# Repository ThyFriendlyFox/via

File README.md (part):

# Via

[Website](https://via.computer) · [Contract](WORKCENTER.md) · [Status](ee-agent-kit/STATUS.md) · [Roadmap](ee-agent-kit/ROADMAP.md)

Via is a workcenter: a set of tools, skills and gates
that an agent steps into to do one kind of work well. Via does
electronics: it turns a KiCad 10 project into fabrication outputs that
passed every gate.

A new board starts with 2 commands. `workcenter new <dir>` writes the
project: a design file to edit, from the template. `workcenter next <dir>`
then names each step, 1 at a time, until the board is GREEN.

<a href="https://via.computer">
  <picture>
    <source media="(prefers-color-scheme: dark)" srcset="site/media/hero-dark.png">
    
  </picture>
</a>

The fixture board `tests/boards/pass-first-design`: lines of its design
file, then the schematic and the routed board that `workcenter design`
writes from the file. The middle card shows the circuit's part of the
sheet.

2 runs of the gates, as the terminal printed them: that board, and a
fixture board with a clearance error on purpose.

```text
$ workcenter gates tests/boards/pass-first-design
PASS   erc        0 errors, 0 warnings  [0.25s]
PASS   drc        0 errors, 0 warnings (0 unconnected, 0 parity), legend (no fab named: held to the least of the 4 fabs Via knows (height pcbway-standard, stroke oshpark-2layer)): 0 fail, 0 not judged  [0.76s]
PASS   sim        1 decks, 46 corner runs, 0 failures  [0.16s]
PASS   export     7/7 outputs, 22 gerber files, 3 files read back  [2.09s]
thermal: no part's junction is judged: sim/thermal.json is not there (the simulate skill, A part's temperature, step 3)
thermal: no part of the board carries a thermal figure in its facts, so no junction is asked for (4 parts; 3 with no facts entry, which `workcenter ratings` names)
RATINGS not asked for: no ratings.json beside the schematic
GREEN: divider  report /home/user/via/tests/boards/pass-first-design/build/gates.json

$ workcenter gates tests/boards/fail-drc-clearance
PASS   erc        0 errors, 0 warnings  [0.3s]
FAIL   drc        1 errors, 1 warnings (0 unconnected, 0 parity), legend (no fab named: held to the least of the 4 fabs Via knows (height pcbway-standard, stroke oshpark-2layer)): 0 fail, 0 not judged  [0.65s]
       - error: clearance: Clearance violation ( clearance 0.2000 mm; actual 0.0500 mm)
       - warning: track_dangling: Track has unconnected end
RATINGS not asked for: no ratings.json beside the schematic
RED: rc_divider  report /home/user/via/tests/boards/fail-drc-clearance/build/gates.json
```

<table>
  <tr>
    <td width="50%"></td>
    <td width="50%"></td>
  </tr>
  <tr>
    <td>The same board, turned. <code>workcenter render</code> draws it with <code>--views spin</code>.</td>
    <td>Each layer that holds something. <code>workcenter render</code> draws 1 picture for each and this sheet.</td>
  </tr>
</table>

The 3D views show the part bodies of KiCad's own library. `install.sh`
installs none of them, and without them the same command draws the bare
board. [site/media/README.md](site/media/README.md) has each picture, how
to fetch the 3 bodies, and the whole command that draws it.

## An example: Herald, a fire alarm communicator

[`examples/fire-alarm-communicator/v0.1`](examples/fire-alarm-communicator/v0.1/README.md) sits
beside a fire alarm panel and reports to a monitoring station over LTE-M, with Wi-Fi as the second
path. 84.4 x 64 mm, 4 layers, every part on the front, red with a white legend and black terminals.
It answers the panel's own phone dialer as if it were the line: a current-limited loop feed, dial
tone and the handshake from a PWM pin, and the panel's DTMF digits decoded in firmware with a
Goertzel filter. 3 supervised inputs read a closed contact, a whole loop and a cut wire apart at
every corner, and a fail-safe relay tells the panel when Herald itself fails.

## An example: Rosetta, a universal controller

[`examples/universal-controller/v0.3`](examples/universal-controller/v0.3/README.md) is a wireless game
controller made with Via: a 5-position knob picks a PS4, a PS5, an Xbox, a Switch or
Bluetooth. Its board is laid out like an Xbox 360 controller's, 148 x 82 mm, 6 layers, routed
and GREEN: thumbsticks soldered on (the footprint written from ALPS's drawing), each in a ring of 8
RGB LEDs; Hall-effect triggers on the shoulder horns; an OLED screen under the dip; 2 back buttons
that set any button to rapid, staggered, burst or pulsed turbo; a cell charged at up to 2.5 A from
USB-C, with a fuel gauge, a buck-boost to 3.3 V, and a power path that runs it as a wired controller
when the cell is flat. An RP2040 runs a second USB port in software to relay a console's signature
to a licensed donor, an ESP32's antenna hangs past the dip between the horns, and 6 decks prove the
knob's 5 positions never meet.

## An example: Signet, a mouse worn as a ring

[`examples/ring-mouse`](examples/ring-mouse/README.md) is a mouse you wear on the index finger, made
with Via as a series of prototypes, a version per pass of a loop. Eight 4-layer boards,
12 mm along the finger, sit on the faces of an octagonal prism round it, each soldered to the next by
8 plated edge pads. The ring turns with the hand and the cursor follows its gyroscope; the thumb slides
along a 3-channel strip to scroll and presses the side to click. A Bluetooth LE module, a charger,
a 3.3 V rail and a 20 mAh cell ride on the other tiles, and every tile is GREEN.

## An example: Hush, a speaker that cancels noise

<table>
  <tr>
    <td width="50%"></td>
    <td width="50%"></td>
  </tr>
</table>

[`examples/anc-speaker/v0.1`](examples/anc-speaker/v0.1/README.md) is a ring 62 mm across that
sits on the face of a 40 mm speaker. A microphone on its hub listens 4 mm in front of the cone, and
an analog feedback loop plays the inverse of what it hears: 7 decks hold 3 dB less noise at 50 Hz
and 12 dB from 200 to 300 Hz at every one of 986 corner runs, and take a 150 Hz hum 18.8 dB down
(13.4 dB at the worst corner). Music from a phone plays through the loop as its target. The back
draws the idea: the noise and its inverse, meeting as one line.

## An example: Wyvern, a Snapdragon development board

[`examples/snapdragon-dev-board`](examples/snapdragon-dev-board/README.md) is a development board
with a Snapdragon on it, laid out like a Teensy and kept as version folders. v0.2 is one flat board,
76.2 x 53.34 mm, 6 layers, 2 rows of 30 pins: a Qualcomm QCS6490 on Vantron's VOSM6490 is soldered
straight on by its 662 pads, a land pattern generated from SGET's OSM standard. An RP2350 beside it
drives the pins at 3.3 V, and Linux flashes it over USB. A buck-boost holds the module's 5.0 V from
any USB-C cable, and an HD3SS3220 switches its USB 3 lane to the side the plug is on; the lane and
the converter's 0.25 mm power pads are drawn by hand in the design file.

## An example: Basalt, a microATX Threadripper board

[`examples/threadripper-matx`](examples/threadripper-matx/README.md) is a workstation motherboard
for an AMD Threadripper on sTR5, on a microATX board (244 x 244 mm), which no maker has built. It is
a prototype series built in a loop logged in its [`LOOP.md`](examples/threadripper-matx/LOOP.md),
one version a feature, each GREEN: v0.1 the floor plan, a 4844-land socket and 14 phases with every
supply in a pour; v0.2 the 4 DDR5 channels, 576 traces drawn by rule with 0 DRC errors on the first
run; v0.3 the ports and headers a desktop board carries, routed by the project's own grid router.
10 layers, black and silver.

## A chip: acc8, an 8-bit processor

Via also takes a chip from RTL to a GDSII mask layout: the drawing a
foundry etches from. The project is Verilog, benches, timing constraints
and `chip.json`. 10 gates run in order on open engines and the open
SkyWater 130 nm process, and stop at the first that does not pass.

<table>
  <tr>
    <td width="50%"></td>
    <td width="50%"></td>
  </tr>
  <tr>
    <td>The layout of <code>tests/chips/pass-acc8</code>, every layer: 760 cells on a die of 152.38 um by 152.38 um. <code>workcenter chip render</code> draws it.</td>
    <td>The second metal layer alone. The command draws 1 picture for each routing layer.</td>
  </tr>
</table>

acc8 is an accumulator processor with 16 opcodes and 4 programs in its
ROM. 5 benches make 1098 checks on the RTL, 4 of them again on the
routed netlist. The run, as the terminal printed it:

```text
$ workcenter chip gates tests/chips/pass-acc8 --strict
PASS   lint       4 RTL files, top acc8, 0 failures  [0.19s]
PASS   sim        5 benches, 1098 checks, 18 of 18 changes of the RTL caught, 0 failures  [0.74s]
PASS   synth      760 cells, 132 flops, 8530.7 um2, the mapping removed 24 flops that nothing reads (--json names each), 0 failures  [1.84s]
PASS   layout     8379.29 um2 of cells, utilisation 0.493, 0 failures  [194.64s]
PASS   sta        15 corners, least setup slack 25.1717 ns at max_ss_n40C_1v60, least hold slack 0.2974 ns at min_ff_n40C_1v95, 0 failures  [4.56s]
PASS   glsim      4 benches on the final netlist, 1 on the RTL only, 0 failures  [0.51s]
PASS   drc        2 decks: magic 0, klayout-mr 0, 0 failures  [15.16s]
PASS   antenna    the routed database, 0 failures  [0.31s]
PASS   lvs        the layout against the netlist with its supply pins: 792 devices against 792, 0 failures  [2.82s]
PASS   export     22 files, 20 reports and manifest.json in chip/tapeout, 0 failures  [0.37s]
scope: open engines, sky130A 1.0.470-0-g6d4d117, decks: magic (community), klayout-mr (community), corners: max_ss_n40C_1v60, max_ss_100C_1v60, max_ff_n40C_1v95, max_ff_100C_1v95, max_tt_025C_1v80, min_ss_n40C_1v60, min_ss_100C_1v60, min_ff_n40C_1v95, min_ff_100C_1v95, min_tt_025C_1v80, nom_ss_n40C_1v60, nom_ss_100C_1v60, nom_ff_n40C_1v95, nom_ff_100C_1v95, nom_tt_025C_1v80; no foundry deck ran; no shuttle's limits were checked
GREEN: pass-acc8  report /home/user/via/tests/chips/pass-acc8/build/gates.json
```

| Gate | What it holds |
|---|---|
| LINT, SIM | The RTL reads the same to a simulator and to a synthesizer. Every bench passes, and every listed change of the RTL fails a bench: a bench that passes on a wrong design proves nothing. |
| SYNTH, LAYOUT | The RTL maps onto the library's cells, with a reset on every flop. The cells are placed and routed with no violation. |
| STA, GLSIM | Timing holds at every corner of temperature and supply the project names, with the routed wires. The benches pass again on the routed netlist. |
| DRC, ANTENNA, LVS | The layout breaks no rule of 2 decks, no wire collects too much charge, and the layout is the netlist, device by device. |
| EXPORT | The layout is handed out only when each of the 9 gates passed on the files as they are now. |

The line before the verdict is the scope of the run. GREEN says that the
open engines found no fault in these files. It does not say that a foundry
accepts the layout or that the silicon works: no foundry deck runs here.

The engines install on request: `sudo ./install.sh --chip`.
`workcenter chip init <dir> --top <module>` starts a project, and
`workcenter next <dir>` names each step from there.
[`.claude/skills/chip-design/SKILL.md`](.claude/skills/chip-design/SKILL.md)
has the procedure, and [`tests/chips/README.md`](tests/chips/README.md)
the 9 fixture chips.

## What it does

| Part | In short |
|---|---|
| **Engines** | KiCad 10 (`kicad-cli`), ngspice, FreeRouting. |
| **Gates** | ERC, DRC, SIM, EXPORT, in that order. A board is done when `workcenter gates <project> --strict` prints GREEN; with a `ratings.json`, that needs its ratings held, and the line above the verdict says whether they are. |
| **Design as code** | `workcenter design design.py --route` builds a schematic and a routed board from a Python file that names parts from the KiCad libraries. No GUI at any step. |
| **A schematic that simulates** | The design file says how each part simulates (`d.sim`, `d.no_sim`), and the schematic KiCad opens exports a netlist ngspice runs. A pin map KiCad would complete by position is refused first. |
| **Decks** | The SIM gate runs the decks under `sim/` and holds each measured value to its bound. A deck is a file of its own. Nothing holds a deck typed by hand to the schematic's parts yet: the roadmap names that gap. |
| **Corners** | The SIM gate runs every deck at each temperature the project names and with each part at each end of its tolerance. It runs every combination of those ends up to 64 runs, and a worst case for each bound above that. It also runs the Monte Carlo draws the project names. A bound holds at every corner or it does not hold. |
| **Frequency plan** | The SIM gate holds every switching frequency and its harmonics against every resonance a deck measured. |
| **The next step** | `workcenter next <project>` names the one step that is left, its command, and the fix for the first failure. A person or an agent of any size follows the same path. |
| **Skills** | Procedures for each kind of step, as Markdown files. |
| **Fixture boards** | The tests. Each passes everything or fails 1 named gate. |

## How it works

<picture>
  <source media="(prefers-color-scheme: dark)" srcset="site/media/diagram-dark.png">
  
</picture>

A design file becomes a KiCad project. The 4 gates judge the project in
order and stop at the first red. The last line of a run is the verdict:
GREEN, RED or SKIPPED. The fabrication outputs of a GREEN board are in
`build/fab/`.

## Quick start

```sh
sudo ./install.sh     # Ubuntu 24.04: KiCad 10, ngspice, Java 21, FreeRouting
workcenter doctor     # each engine's status; ok when nothing is absent
workcenter gates tests/boards/pass-first-design     # GREEN
workcenter gates tests/boards/fail-drc-clearance    # red at DRC, on purpose
workcenter next tests/boards/fail-drc-clearance     # the one next step: the fix
workcenter sim tests/boards/fail-sim-corner         # red at its corners, on purpose
workcenter sim tests/boards/fail-freq-overlap       # red on the frequency plan
```

On your own computer the install has no time limit: a slow line finishes, and apt gives up a stalled file by itself; to set one, pass it through sudo with env (`sudo env APT_DOWNLOAD_TIMEOUT=900 ./install.sh`). CI sets `APT_UPDATE_TIMEOUT=120 APT_DOWNLOAD_TIMEOUT=570`, so a stall ends with apt's own line before the job's limit. Run the script as a file, not through a pipe or `bash <(...)`.

Output goes to `<project>/build/`: `erc.json`, `drc.json`, `sim/`,
`fab/` (gerbers, drill, BOM, schematic PDF), `gates.json`.

A first board starts in a folder of its own outside this checkout:

```sh
workcenter new ~/divider                         # design.py from the template, .gitignore, parts.csv, library/sources.csv
workcenter next ~/divider                        # the one next step: here, the design
workcenter design ~/divider/design.py --route    # the KiCad project, routed
workcenter gates ~/divider --strict              # GREEN, and SIM has no deck to run yet
```

[`.claude/skills/board-design/SKILL.md`](.claude/skills/board-design/SKILL.md)
has the procedure from a spec to a GREEN board.

## Commands

`workcenter --help` describes each command, and
`workcenter <command> --help` lists its flags.
[`ee-agent-kit/docs/CONFIGURATION.md`](ee-agent-kit/docs/CONFIGURATION.md)
has every flag.

<details>
<summary>The 38 commands</summary>

| Command | What |
|---|---|
| `doctor` | Report each engine's status. |
| `next` | Name the one next step for a project. |
| `new` | Start a board project in a folder: the template's design file under the folder's name, `.gitignore`, `parts.csv` and `library/sources.csv` with their headers. Refuses a folder that holds a design. |
| `chip` | A chip project, from RTL to a GDSII layout: `chip init`, `chip gates`, 1 command for each of its 10 gates, and `chip render` for a picture of the layout. Tests hold all 10 gates. The acceptance design, an 8-bit processor of 760 cells on the sky130A process, is GREEN with `--strict` in under 4 minutes. |
| `design` | Build a design file into a KiCad project; `--route` routes it; `--check` compares every file it writes but the board and names the 1 step; `--rules-only` writes the copied fab rule file again and nothing else. |
| `erc`, `drc`, `sim`, `export` | One gate, alone. |
| `gates` | The 4 gates in order; the last line is the verdict. |
| `verify` | Check a verification package against a fresh run; say whether the requirements are met. |
| `ratings` | Hold a schematic to its parts' ratings: each pin's voltage limits, each part's derating by a named standard, each regulator's output, load and support parts. Every limit names its document, and a pack's rule and a pin's limit their page. |
| `references` | The index of the standards, notes, datasheets, reports, web pages, papers and books the rules and the code cite, each held by the SHA256 of its copy, a web page by the values read from it: `fetch` gets each once under Via's own name into a folder outside the repository, `check` judges a file a person downloaded, `rules` fails a rule or a tool's `CITES` whose document the index lacks. |
| `measure` | Write the plan of measurements for a built board: for each sim bound the pad to probe, the reference pad, the instrument, the span the reading must fall in and the predicted value, as written and over the corners. |
| `now` | The work card of 1 piece of work in progress: its `**Status:**` line for the project board (Todo, In progress or Done), its branch and last commit, what is done now, the last health gate, what it waits for and what is left. 1 issue's body per piece of work, titled `Work card: ...` and rewritten in place; `--write` puts it on the `status` branch for a host without GitHub. |
| `standards` | List each requirement of the product kind `product.json` names, from free documents, as held by a gate, held by a named test of the verification package, or not held, with the document and clause. A list, not a certificate. |
| `image` | The content tag of the toolchain's files (`Dockerfile`, `install.sh`, `requirements.txt`) at a commit, the name of the image of that tag, and in the image the record of its build: tag, commit, machine, the tools' versions. Runs no engine. |
| `mcp` | An MCP server on stdio (revision 2025-11-25) for a host that is not Claude Code: `doctor`, `gates`, `erc`, `drc`, `sim`, `export` and `autoroute` as tools, each running its command and answering its lines and exit code. Every path a call names must lie inside the folder the server was given. Writes only MCP messages to stdout. |
| `legend` | Hold every text printed on a board to its fab's least height and stroke and to no overlap, no hidden or stray designator and 2 directions a side, from the board file; `--place OUT` writes a copy with each designator placed. |
| `highspeed` | Hold the fast pairs that `interfaces.json` names to their interface's document: the width a cross-section solver gives for its impedance on the board's stackup at the gap the tracks have, the gap, the length, the skew within a pair, the vias, and an unbroken ground plane above and below; write the same limits as KiCad rules. |
| `copper` | Hold a routed board's power nets to a greatest voltage drop and current density on their own copper and in each via's barrel, and the board to a greatest temperature from its parts' heat; draw each as a picture. Every constant names its document; every limit is the project's. |
| `fields` | Simulate the critical nets `fields.json` names with openEMS, from the board file, and hold impedance, loss and coupling to their limits. |
| `bench` | Route design files with each router and compare: time, share joined, DRC errors, commands, bytes read. |
| `autoroute` | Route a hand-drawn board headless with `--apply`: the `.kicad_pcb` is read, routed by FreeRouting and written in place, then checked by DRC. Without `--apply`, write FreeRouting's session file for a DSN exported from KiCad. |
| `inspect` | Read a routed board: `map`, `list`, `probe`, `net`, `islands`, `resistance`, `crossed`. |
| `placement` | Run a kistack placement check on a board. |
| `render`, `pictures` | Images of the schematic, the board, every layer; turning GIFs; assembly scenes. |
| `procure`, `costs` | Price a board's parts; price every board of every version. |
| `sources`, `fetch`, `curve` | Check each part's datasheet and model; fetch one, or keep one a person downloaded, and refuse a web page saved as a PDF; read a curve from a PDF. |
| `mutate` | Prove a firmware's host tests can fail. |
| `ci` | Replay a repository's GitHub workflow here. |
| `docs`, `version`, `diagram` | A version's contents page and datasheets, and with `--check` the 2 held to what `docs` writes; a new version folder; a block diagram. |

</details>

## Where it runs

**A Claude Code cloud environment.** The environment carries the
software; the project's repository carries the board. Create an environment
whose setup script is the 3 lines in
[`environment/setup.sh`](environment/setup.sh), with the network hosts from
[`environment/README.md`](environment/README.md). Open any project's
repository in it. Attach this repository as a second repository when its
skills should load.

**Another agent host.** `AGENTS.md` at the root is the entry for a host
that does not read `CLAUDE.md`; the 2 files are the same text. Every
procedure is a Markdown file under `.claude/skills/`, and every check is a
command. `workcenter next <project>` gives the step, and `make verify`
the repository's health.

**A Docker image.** With Docker instead of installing (amd64 or arm64; no openEMS on arm64):
`docker run --rm --user "$(id -u):$(id -g)" -v "$PWD":/work ghcr.io/thyfriendlyfox/via:main workcenter gates .`.
The files the gates write belong to you. The image holds the toolchain install.sh installs and Via, without the example boards and the site; `.github/workflows/image.yml` builds it on Ubuntu 24.04 and publishes it from `main`, a release's tag, each Monday and by hand. Pin a toolchain by its digest from the `Image` workflow's summary. The package is named `via`. Its first image is pushed by the release's tag or the next push to `main`; the images built before the first release went to an older package, `ee-workcenter`, which is no longer updated.

### Run Via from its container

The image of the release v0.1.0 has the tag `v0.1.0`.
It mounts your project on `/work`, its working folder.

Pull the image:

```sh
docker pull ghcr.io/thyfriendlyfox/via:v0.1.0
```

Run the gates on the project in the current folder, on Linux or macOS in a POSIX shell:

```sh
docker run --rm --user "$(id -u):$(id -g)" -v "$PWD":/work ghcr.io/thyfriendlyfox/via:v0.1.0 workcenter gates .
```

On Windows, in PowerShell:

```powershell
docker run --rm -v "${PWD}:/work" ghcr.io/thyfriendlyfox/via:v0.1.0 workcenter gates .
```

On Windows, in cmd.exe:

```bat
docker run --rm -v "%cd%:/work" ghcr.io/thyfriendlyfox/via:v0.1.0 workcenter gates .
```

- On Linux, `--user` makes the files the gates write yours; the image's build checks this with the same command.
- With no command, the image runs `workcenter doctor`.
- The package is public: a pull needs no login.
- On arm64 (an Apple Silicon Mac, a Windows on Arm PC) the image has no openEMS; `--platform linux/amd64` runs the amd64 image, with openEMS, under emulation.
- Docker Desktop on Windows and macOS runs Linux containers, and this image is a Linux image (Ubuntu 24.04).
- The chip engines are not in the image; `sudo ./install.sh --chip` installs them on Ubuntu 24.04.
- The image build runs the Linux command on Linux; nobody has run these commands on Windows or macOS yet.

A board repository gets the gates on every pull request from 1 workflow that calls `ThyFriendlyFox/via/.github/workflows/board-gates.yml@main`: 1 job per project folder, the gates table in the job's summary, a red check on RED, SKIPPED, or a project with no board to judge. It runs in Via's public image, and installs with install.sh where the registry holds no image of that toolchain. The `board-ci` skill holds the caller.

## The website

`site/` is the project's website: a home page with real runs of the
commands, drawings of what each gate catches and the board above, and a
page for each example, written by `site/examples.py` from the example's
README, its `TIMELINE.md` and its board. It is live at <https://via.computer>.
`python3 -m http.server 8000 --directory site` serves it at
http://localhost:8000. Vercel deploys a push that changes `site/`: `main`
to production, any other branch to a preview.
[`site/README.md`](site/README.md) has the commands, the files and how the
images are drawn.

## Repository map

<details>
<summary>Each path and what it holds</summary>

| Path | What |
|---|---|
| `install.sh` | The only source of the toolchain. |
| `Makefile`, `verify/` | `make verify`: the repository's health gate, one command, run by CI's `full` job; `make check`: the fast checks before a push to a work branch, with `make kit`, the gate's kit checks alone; `verify/testshards.py` runs its tests in shards side by side by `verify/shards.csv` (`verify/README.md`). |
| `tools/workcenter` | The CLI and the gates. Standard library only. |
| `tools/kicadgen.py` | Design a board in Python from the KiCad libraries; writes the KiCad project and routes it headless. |
| `tools/simcorners.py`, `tools/freqplan.py`, `tools/thermal.py`, `tools/simneeds.py` | The corners a deck runs at; the frequency plan; each part's junction temperature at every run; the decks the schematic asks for. Read by the SIM gate. |
| `tools/partdata.py` | The makers' data of a deck's capacitors and inductors: picks each curve from the part's facts when its maker's file has its row in `library/sources.csv`, and rewrites the deck's part as ngspice's behavioural element on it. Standard library only; the SIM gate runs it. |
| `tools/guide.py` | `workcenter next`: the one next step and the fix for each kind of failure. |
| `tools/newboard.py` | `workcenter new`: a board project from `templates/project/`, with the headers of the parts file and of `library/sources.csv`. Standard library only. |
| `tools/enginelock.py` | The engine lock: long `workcenter` commands take turns on 1 machine in the order they came, and `make verify` holds it for the whole gate; `hold`, `held` and `state` on its own command line. Standard library only. |
| `tools/clock.py` | The day and the time a command runs at: 1 reading at its start, pinned by `SOURCE_DATE_EPOCH`; the machine's day for a price's age and the machine's clock for the engine lock; and the reader of a file's calls of the clock that 2 tests hold the tools and the test files to. Standard library only. |
| `tools/ratings.py` | `workcenter ratings`: the voltage span of each net, the facts of each part, and each stress against its limit. Standard library only. |
| `tools/blocks.py` | Circuit blocks a design file adds in 1 call, each written from its maker's note: `blocks.buck`, a buck regulator by TI SLVA477C, and the entry points of the other blocks; their numbers in `rules/blocks/`. |
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
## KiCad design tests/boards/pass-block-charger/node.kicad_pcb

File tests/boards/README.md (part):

# Fixture boards

These projects are the tests of the gates. Each one exists to make 1 gate
behave in a known way.

| Project | Expected | Why |
|---|---|---|
| `pass-rc-divider` | GREEN on `workcenter gates`, with `--strict` too | A 2-resistor divider with an RC filter. Schematic, board, and a sim deck with bounds. Its `sim/corners.json` names -40 and 85 C, 1 % resistors, a 10 % capacitor and 8 Monte Carlo draws: 46 corner runs, the output between 2.4605 and 2.54175 V, 8.25 mV inside its nearer bound. |
| `pass-first-design` | GREEN on `workcenter gates`, with `--strict` too | The first design file, built: the 1 fixture that goes from a design file through all 4 gates. `design.py` is `templates/project/design.py` to the byte. The schematic and the project file are what `workcenter design` writes from it; a test compares. `workcenter design design.py --route` wrote the board, and DRC holds the board to the schematic. On a 5 V supply the deck holds 2 bounds over 46 corner runs. The output stays between 2.4605 and 2.5417 V, and `f3` between 280.2 and 365.5 Hz. `f3` is the frequency where the output is 0.3536 of the input: the low-pass corner at a gain of 0.5. The pictures of the root `README.md` are of this board. |
| `fail-drc-clearance` | ERC pass, DRC fail with a `clearance` violation | The same board with 1 track moved inside the clearance of a pad. |
| `route-me` | DRC with 5 unconnected items before `workcenter autoroute --apply`, 0 after, with `--strict` too | A hand-drawn board for ROADMAP item 15: the divider's 4 parts with R2 on the back and C1 turned 90 degrees, and only VIN drawn (3 tracks). VOUT's 4 pads need 3 connections and GND's 3 pads need 2. `tests/test_gates.py::test_autoroute_apply_routes_fixture` routes a copy; `tests/test_boardroute.py` reads it with a stand-in router. |
| `fail-sim-spec` | SIM fail on the `vout` bound | The divider deck with bounds that the circuit cannot meet. No board, no corners: the gate names their absence as a warning. |
| `fail-sim-corner` | SIM fail at a corner, each bound holding as written | 2 decks, no board. `diode_ref`: a diode's forward voltage, 0.548 V at 27 C and 0.42 V at 85 C against a 0.50 to 0.60 V window. `divider`: 2.5 V as written, 2.375 V and 2.625 V with its 5 % resistors apart against 2.45 to 2.55 V. 32 corner runs; each failure line names the worst corner and how many more miss. |
| `pass-lc-filter` | SIM pass with `--strict` | 3 decks, no board: a 15.9 kHz input filter swept with `.ac`, a 100 kHz load clear of it, and a 16 kHz clock on its resonance. `sim/frequency-plan.json` names both sources and the resonance, and answers the clock's overlap with the deck that drives it. 94 corner runs: the deck that answers the overlap is also run with L stepped against C between their ends. |
| `fail-freq-overlap` | SIM fail on the frequency plan alone | The same filter with a load at 5.3 kHz, whose third harmonic is the resonance: the rail swings 6.8 V on a 5 V supply while the deck's one bound, on the average, holds. Only the plan sees it. |
| `inspect-four-layer` | `workcenter inspect` answers as `tests/test_inspect.py` expects; DRC fails with 1 unconnected item, the pour island it keeps on purpose | Generated from its own `design.py` (regenerate with `workcenter design`; a test compares). Four layers, VIN's 10 mm run on In2.Cu between two vias, a T-junction, a copper keep-out over the island, a parts keep-out, Sierra's rule file. |
| `fail-fab-sierra` | GREEN on `workcenter gates --strict`, DRC fail with `--fab sierra-circuits-web` (`annular_width`, `text_thickness`) | The divider with a 0.6/0.3 mm via (0.15 mm ring, under Sierra's 6 mil) on a bottom-face return of VOUT, and a legend label stroked 0.10 mm (under 5 mil). |
| `pass-board-ecss` | DRC pass with `--strict`: `board rules ecss-q-st-70-12c-rev1: 0 fail, 0 not judged` | The divider on an 80 x 80 mm outline, 1.6 mm thick, with `board-rules.json` naming ECSS-Q-ST-70-12C Rev.1. Its `ratings.json` states VIN 0 to 5.25 V, VOUT 0 to 2.625 V, GND 0 V, and 1 A on J1 pins 1 and 3. Every gap is 5.25 V at most, so 0.25 mm as designed on an outer layer (table 13-7, page 130). VIN and GND are drawn 1.4 mm: 1 A asks 0.752 mm, and VIN beside GND, under 25 mm apart, is 1 conductor of 2 A that asks 0.064379 mm2 as manufactured, where the 2 give 0.0675 mm2 (13.6.3g; `tests/test_boardrules_drc.py` works both out). Its `ratings` judges nothing (no parts file), so `gates --strict` ends `RED (ratings not held)`; `tests/test_done.py` names it. |
| `fail-board-ecss` | DRC fail on 2 lines of the pack, 0 errors of KiCad's own | The same board with 1 VIN segment left at 0.25 mm, and a GND stub on B.Cu that ends 0.22 mm from J1 pin 1 (VIN). KiCad also warns that the stub has an unconnected end: a warning, which fails only a `--strict` run. Its `ratings` judges nothing (no parts file), so `gates --strict` ends `RED (ratings not held)`; `tests/test_done.py` names it. |
| `pass-layout` | DRC pass with `--strict`: `board rules ti-slva680a-esd + ti-szza009-emi: 0 fail, 0 not judged` | The board of `layout_board.py`, 2 layers: a 4-pin header J1 (VBUS, DA, DB, GND), a TVS from each of its 3 lines to GND beside it, C1 on VBUS, R1 and R2 on the data lines 6.54 mm from their TVS, GND poured on both faces. VBUS is 1.2 mm wide: 2.55 mm to D1 and 2.8875 mm on to C1, at most 2.41 to 1. Generated from its `design.py`. |
| `fail-layout-esd` | DRC fail on 4 lines, of each rule of `ti-slva680a-esd`, 0 of KiCad's own | VBUS reaches D1 from J1 on B.Cu and a via (`no-via`), and that detour is 4.67 mm of copper while C1.1 lies 2.89 mm from D1.1 (`nearest`); D2 stands 4.35 mm from J1.2 and R1.1 3.94 mm from D2 (`nearest`); DB has no TVS (`protector`). |
| `fail-layout-emi` | DRC fail on 1 line, the rule of `ti-szza009-emi`, 0 of KiCad's own | C1 stands 0.8 mm further: 3.6875 mm of 1.2 mm VBUS from D1, 3.07 to 1. |
| `fail-layout-tee` | DRC fail on 1 line, the rule `nearest` of `ti-slva680a-esd`, 0 of KiCad's own | VBUS branches at J1.1: 4.35 mm across to D1.1 and 2.8875 mm up to C1.1, both 1.5 mm wide. C1.1 (centre 101.15) stands 5.20 mm from D1.1 and lies 7.24 mm of copper from it, further than D1.1 from J1.1, but stands 2.85 mm from J1.1, nearer than D1.1 (SLVA680A section 2.3, Case 2). |
| `pass-creepage` | DRC pass with `--strict`: `board rules mil-hdbk-454c-g69: 0 fail, 0 not judged` | The board of `creepage_board.py`: 2 single pins, J1 on /HV and J2 on GND, 1.7 mm square pads on both faces, centres 5 mm apart: 3.3 mm. `ratings.json` puts /HV at 0 to 400 V. MIL-HDBK-454C table 69-I, page 69-2, 300 to 600 V, condition A, enclosure I: clearance 1.5 mm, leakage 3 mm. |
| `fail-creepage` | DRC fail on 2 lines, creepage on F.Cu and on B.Cu, 0 of KiCad's own | The same board with the centres 3.7 mm apart: 2 mm, under the 3 mm of leakage distance; the clearance of 1.5 mm holds. |
| `pass-creepage-slot` | DRC pass (default gate): `board rules ti-slup419-creepage: 0 fail, 2 not judged`, the 2 `not judged clearance` lines of a pack with no clearance table; `--strict` fails on them | The pass board with a slot cut from (112, 105) to (113, 110). SLUP419 table 3, page 7, pollution degree 2, group III, 400 V: 4.0 mm. 3.3 mm straight; round the slot 2 x sqrt(1.15^2 + 1.65^2) + 1 = 5.022 mm. Table 7, page 11: a slot counts from 1.0 mm at degree 2. SLUP419 takes clearance from an impulse voltage (page 7), so each face's pair is `not judged` for clearance. |
| `fail-creepage-clearance` | DRC fail on 4 lines, clearance and creepage on F.Cu and on B.Cu, 0 of KiCad's own | The pass board with the centres 3 mm apart: 1.3 mm, under the 1.5 mm of clearance and the 3 mm of leakage distance of MIL-HDBK-454C table 69-I, page 69-2. It breaks both rules of the pack. |
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
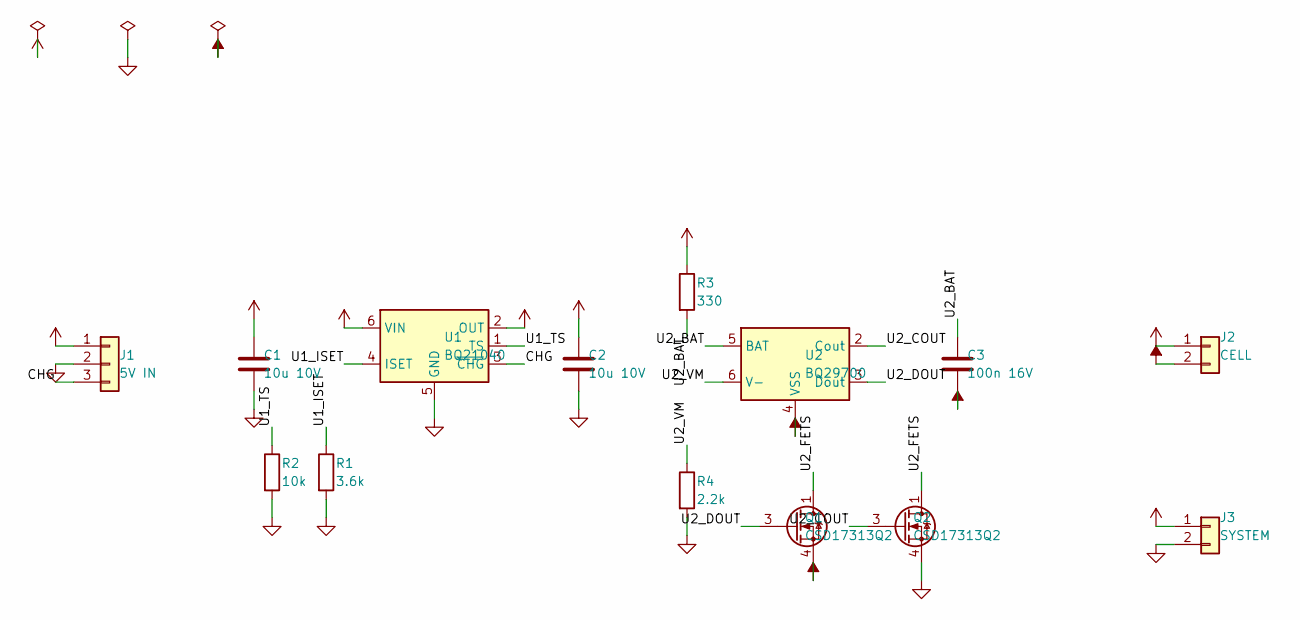
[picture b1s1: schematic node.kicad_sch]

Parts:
C1, C2: 10u 10V; C_0603_1608Metric
C3: 100n 16V; C_0603_1608Metric
J1: 5V IN; PinHeader_1x03_P2.54mm_Vertical
J2: CELL; PinHeader_1x02_P2.54mm_Vertical
J3: SYSTEM; PinHeader_1x02_P2.54mm_Vertical
Q1, Q2: CSD17313Q2; Texas_DQK
R1: 3.6k; R_0603_1608Metric
R2: 10k; R_0603_1608Metric
R3: 330; R_0603_1608Metric
R4: 2.2k; R_0603_1608Metric
U1: BQ21040; SOT-23-6
U2: BQ29700; WSON-6_1.5x1.5mm_P0.5mm

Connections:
+5V: C1.1, J1.1, U1.6 (VIN)
+BATT: C2.1, J2.1, J3.1, R3.1, U1.2 (OUT)
-BATT: C3.2, J2.2, Q1.4 (S), Q1.7 (S), U2.4 (VSS)
/CHG: J1.3, U1.3 (~CHG)
/U1_ISET: R1.1, U1.4 (ISET)
/U1_TS: R2.1, U1.1 (TS)
/U2_BAT: C3.1, R3.2, U2.5 (BAT)
/U2_COUT: Q2.3 (G), U2.2 (Cout)
/U2_DOUT: Q1.3 (G), U2.3 (Dout)
/U2_FETS: Q1.1 (D), Q1.2 (D), Q1.5 (D), Q1.6 (D), Q1.8 (D), Q2.1 (D), Q2.2 (D), Q2.5 (D), Q2.6 (D), Q2.8 (D)
/U2_VM: R4.1, U2.6 (V-)
GND: C1.2, C2.2, J1.2, J3.2, Q2.4 (S), Q2.7 (S), R1.2, R2.2, R4.2, U1.5 (GND)

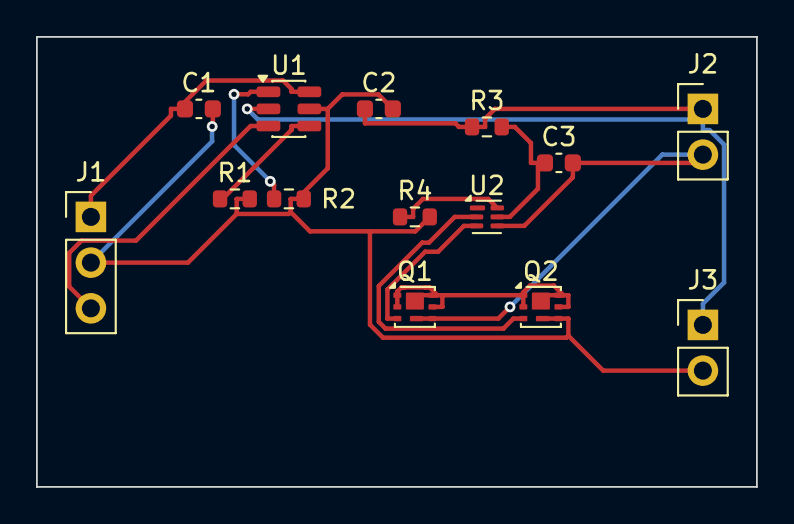
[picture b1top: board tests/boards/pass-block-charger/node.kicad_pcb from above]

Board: 2 copper layers, 40.0 x 25.0 mm, 14 parts (0 on the bottom side), 12 nets.

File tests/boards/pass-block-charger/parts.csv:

Value,Footprint,Qty,Manufacturer,MPN,Supplier,SKU,Pack,Breaks
BQ21040,Package_TO_SOT_SMD:SOT-23-6,1,Texas Instruments,BQ21040DBVR,,,,
3.6k,Resistor_SMD:R_0603_1608Metric,1,Vishay,CRCW06033K60FKEA,,,,
10k,Resistor_SMD:R_0603_1608Metric,1,Vishay,CRCW060310K0FKEA,,,,
10u 10V,Capacitor_SMD:C_0603_1608Metric,2,Samsung,CL10A106KP8NNN,,,,
BQ29700,Package_SON:WSON-6_1.5x1.5mm_P0.5mm,1,Texas Instruments,BQ29700DSER,,,,
330,Resistor_SMD:R_0603_1608Metric,1,Vishay,CRCW0603330RFKEA,,,,
100n 16V,Capacitor_SMD:C_0603_1608Metric,1,Vishay,VJ0603Y104KXJAC,,,,
2.2k,Resistor_SMD:R_0603_1608Metric,1,Vishay,CRCW06032K20FKEA,,,,
CSD17313Q2,Package_SON:Texas_DQK,2,Texas Instruments,CSD17313Q2,,,,

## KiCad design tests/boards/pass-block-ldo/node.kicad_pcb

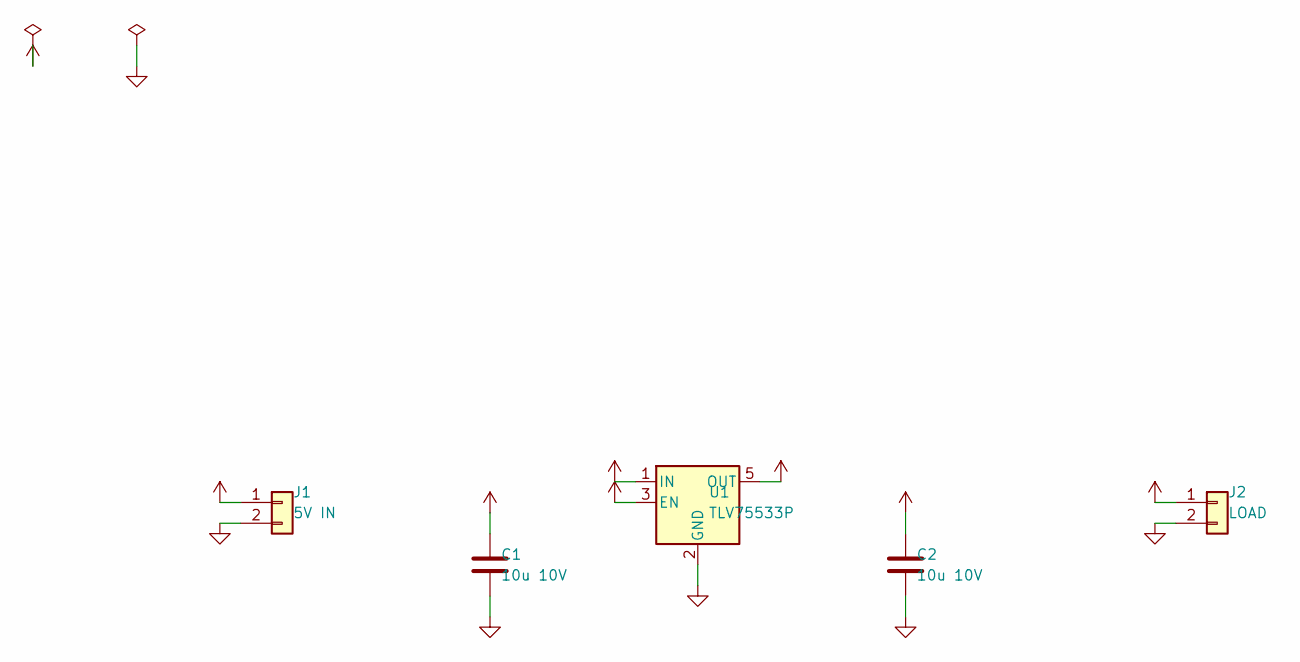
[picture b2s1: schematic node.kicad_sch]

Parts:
C1, C2: 10u 10V; C_0603_1608Metric
J1: 5V IN; PinHeader_1x02_P2.54mm_Vertical
J2: LOAD; PinHeader_1x02_P2.54mm_Vertical
U1: TLV75533P; SOT-23-5

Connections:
+3V3: C2.1, J2.1, U1.5 (OUT)
+5V: C1.1, J1.1, U1.1 (IN), U1.3 (EN)
GND: C1.2, C2.2, J1.2, J2.2, U1.2 (GND)

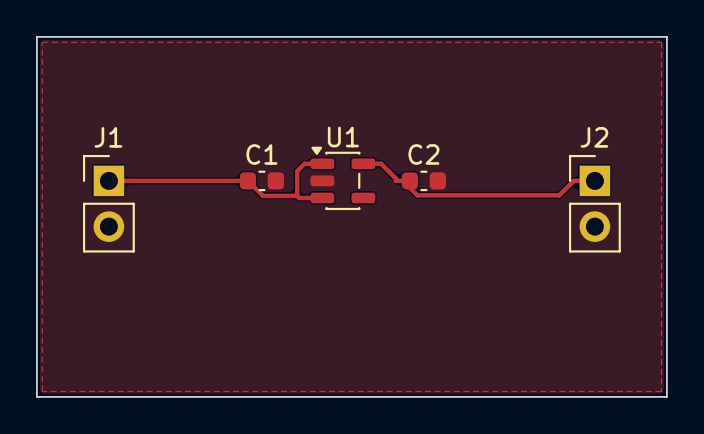
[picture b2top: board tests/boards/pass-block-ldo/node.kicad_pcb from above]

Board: 2 copper layers, 35.0 x 20.0 mm, 5 parts (0 on the bottom side), 3 nets.

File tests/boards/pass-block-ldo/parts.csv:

Value,Footprint,Qty,Manufacturer,MPN,Supplier,SKU,Pack,Breaks
TLV75533P,Package_TO_SOT_SMD:SOT-23-5,1,Texas Instruments,TLV75533PDBVR,,,,
10u 10V,Capacitor_SMD:C_0603_1608Metric,2,Samsung,CL10A106KP8NNN,,,,

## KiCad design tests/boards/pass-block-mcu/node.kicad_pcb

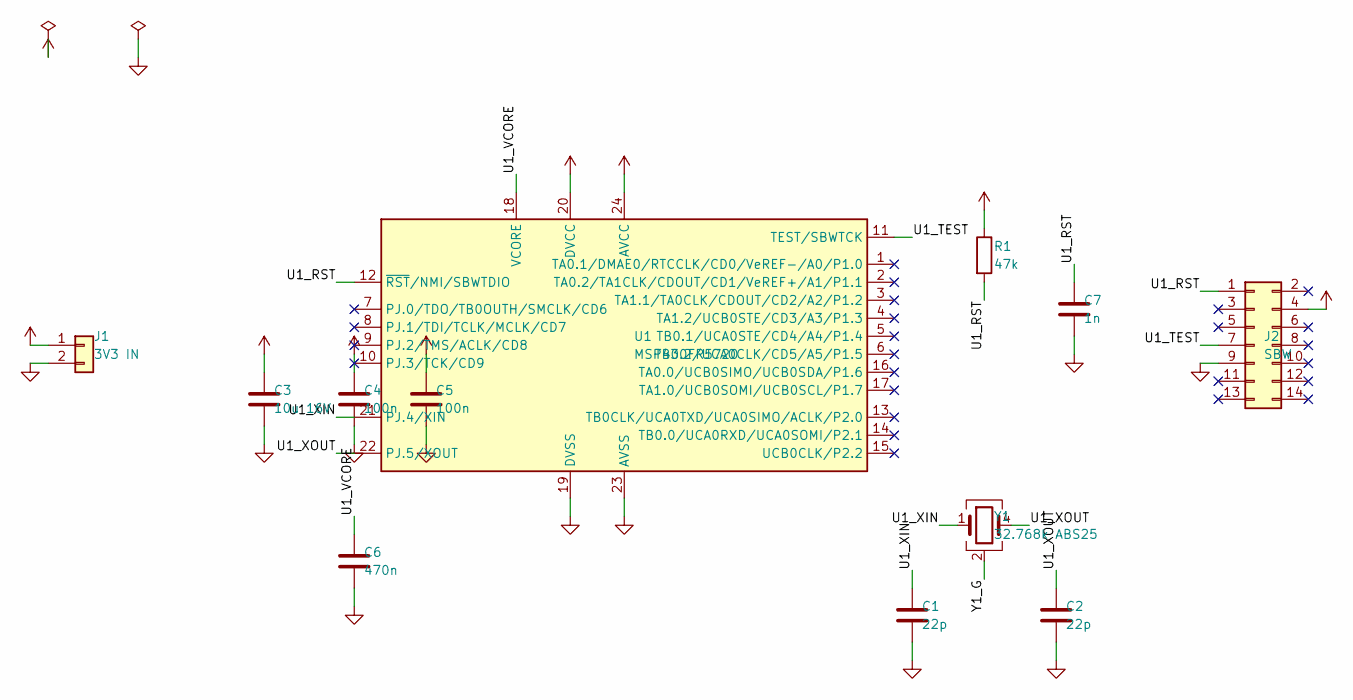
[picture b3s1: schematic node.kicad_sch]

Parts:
C1, C2: 22p; C_0603_1608Metric
C3: 10u 16V; C_0805_2012Metric
C4, C5: 100n; C_0603_1608Metric
C6: 470n; C_0805_2012Metric
C7: 1n; C_0603_1608Metric
J1: 3V3 IN; PinHeader_1x02_P2.54mm_Vertical
J2: SBW; PinHeader_2x07_P2.54mm_Vertical
R1: 47k; R_0603_1608Metric
U1: MSP430FR5720; Texas_RGE0024C_VQFN-24-1EP_4x4mm_P0.5mm_EP2.1x2.1mm
Y1: 32.768k ABS25; Crystal_SMD_Abracon_ABS25-4Pin_8.0x3.8mm

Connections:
+3V3: C3.1, C4.1, C5.1, J1.1, J2.4, R1.1, U1.20 (DVCC), U1.24 (AVCC)
/U1_RST: C7.1, J2.1, R1.2, U1.12 (~RST/NMI/SBWTDIO)
/U1_TEST: J2.7, U1.11 (TEST/SBWTCK)
/U1_VCORE: C6.1, U1.18 (VCORE)
/U1_XIN: C1.1, U1.21 (PJ.4/XIN), Y1.1
/U1_XOUT: C2.1, U1.22 (PJ.5/XOUT), Y1.4
/Y1_G: Y1.2 (G), Y1.3 (G)
GND: C1.2, C2.2, C3.2, C4.2, C5.2, C6.2, C7.2, J1.2, J2.9, U1.19 (DVSS), U1.23 (AVSS)

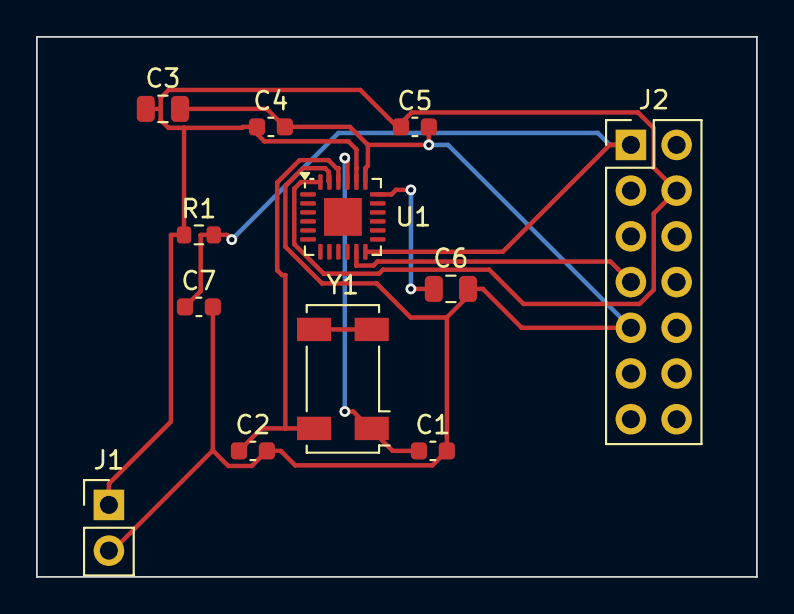
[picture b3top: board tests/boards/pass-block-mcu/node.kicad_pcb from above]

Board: 2 copper layers, 40.0 x 30.0 mm, 12 parts (0 on the bottom side), 8 nets.

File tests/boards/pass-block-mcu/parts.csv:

Value,Footprint,Qty,Manufacturer,MPN,Supplier,SKU,Pack,Breaks
MSP430FR5720,Package_DFN_QFN:Texas_RGE0024C_VQFN-24-1EP_4x4mm_P0.5mm_EP2.1x2.1mm,1,Texas Instruments,MSP430FR5720IRGE,,,,
32.768k ABS25,Crystal:Crystal_SMD_Abracon_ABS25-4Pin_8.0x3.8mm,1,Abracon,ABS25-32.768KHZ-12-T,,,,
22p,Capacitor_SMD:C_0603_1608Metric,2,Vishay,VJ0603A220JXAAC,,,,
10u 16V,Capacitor_SMD:C_0805_2012Metric,1,made up,FIXTURE-10U-16V,,,,
100n,Capacitor_SMD:C_0603_1608Metric,2,Vishay,VJ0603Y104KXJAC,,,,
470n,Capacitor_SMD:C_0805_2012Metric,1,Vishay,VJ0805Y474KXJAC,,,,
47k,Resistor_SMD:R_0603_1608Metric,1,Vishay,CRCW060347K0FKEA,,,,
1n,Capacitor_SMD:C_0603_1608Metric,1,Vishay,VJ0603Y102KXJAC,,,,
SBW,Connector_PinHeader_2.54mm:PinHeader_2x07_P2.54mm_Vertical,1,,,,,,

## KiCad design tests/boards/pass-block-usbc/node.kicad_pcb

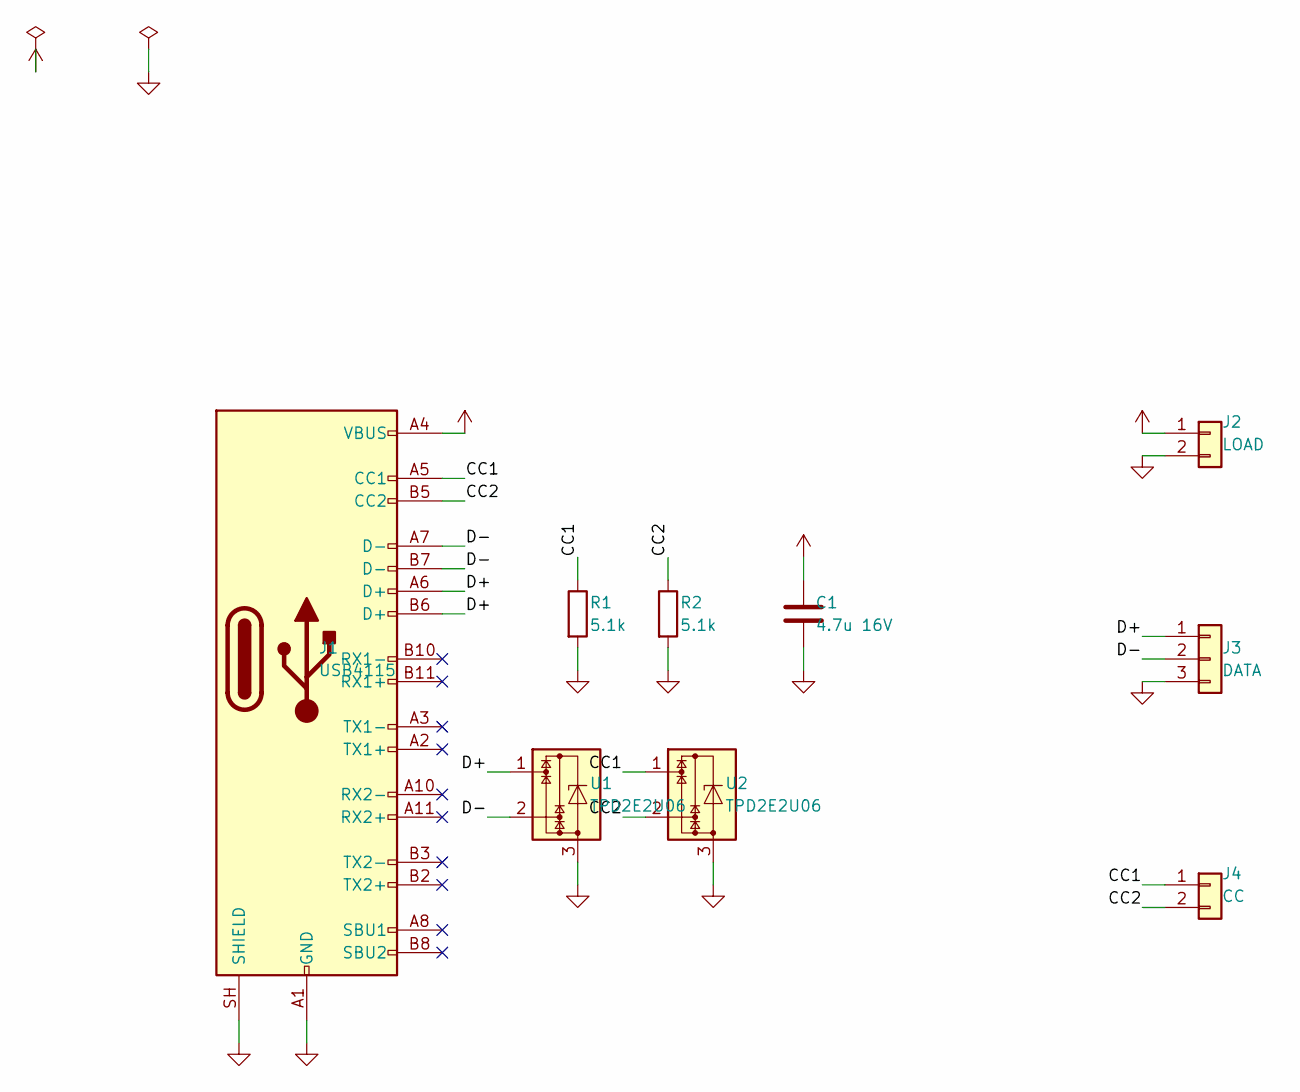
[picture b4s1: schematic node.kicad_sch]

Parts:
C1: 4.7u 16V; C_0603_1608Metric
J1: USB4115; USB_C_Receptacle_GCT_USB4115-03-C
J2: LOAD; PinHeader_1x02_P2.54mm_Vertical
J3: DATA; PinHeader_1x03_P2.54mm_Vertical
J4: CC; PinHeader_1x02_P2.54mm_Vertical
R1, R2: 5.1k; R_0603_1608Metric
U1, U2: TPD2E2U06; SOT-323_SC-70

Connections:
/CC1: J1.A5 (CC1), J4.1, R1.1, U2.1
/CC2: J1.B5 (CC2), J4.2, R2.1, U2.2
/D+: J1.A6 (D+), J1.B6 (D+), J3.1, U1.1
/D-: J1.A7 (D-), J1.B7 (D-), J3.2, U1.2
GND: C1.2, J1.A1 (GND), J1.A12 (GND), J1.B1 (GND), J1.B12 (GND), J1.SH (SHIELD), J2.2, J3.3, R1.2, R2.2, U1.3, U2.3
VBUS: C1.1, J1.A4 (VBUS), J1.A9 (VBUS), J1.B4 (VBUS), J1.B9 (VBUS), J2.1

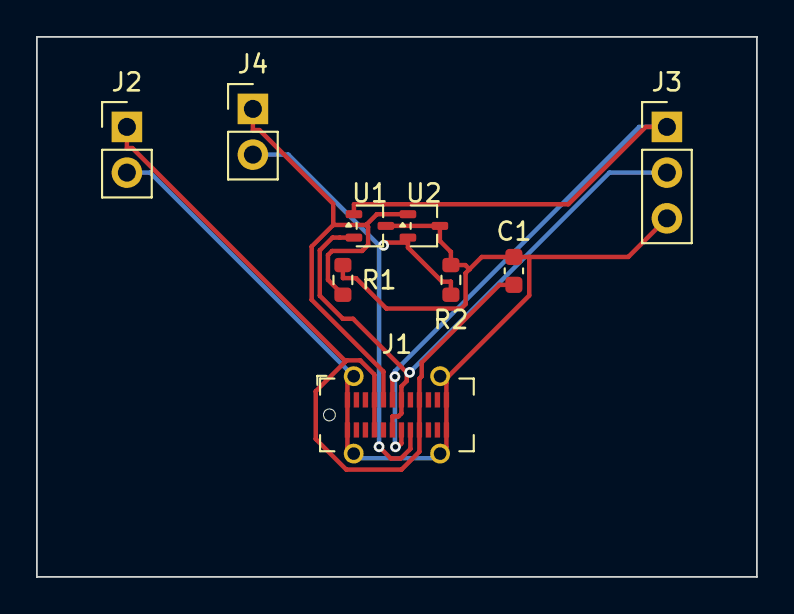
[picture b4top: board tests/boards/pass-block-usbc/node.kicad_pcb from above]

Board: 2 copper layers, 40.0 x 30.0 mm, 9 parts (0 on the bottom side), 6 nets.

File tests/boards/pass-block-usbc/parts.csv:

Value,Footprint,Qty,Manufacturer,MPN,Supplier,SKU,Pack,Breaks
USB4115,Connector_USB:USB_C_Receptacle_GCT_USB4115-03-C,1,GCT,USB4115-03-C,,,,
5.1k,Resistor_SMD:R_0603_1608Metric,2,Vishay,CRCW06035K10FKEA,,,,
TPD2E2U06,Package_TO_SOT_SMD:SOT-323_SC-70,2,Texas Instruments,TPD2E2U06DCKR,,,,
4.7u 16V,Capacitor_SMD:C_0603_1608Metric,1,Samsung,CL10A475KO8NNN,,,,

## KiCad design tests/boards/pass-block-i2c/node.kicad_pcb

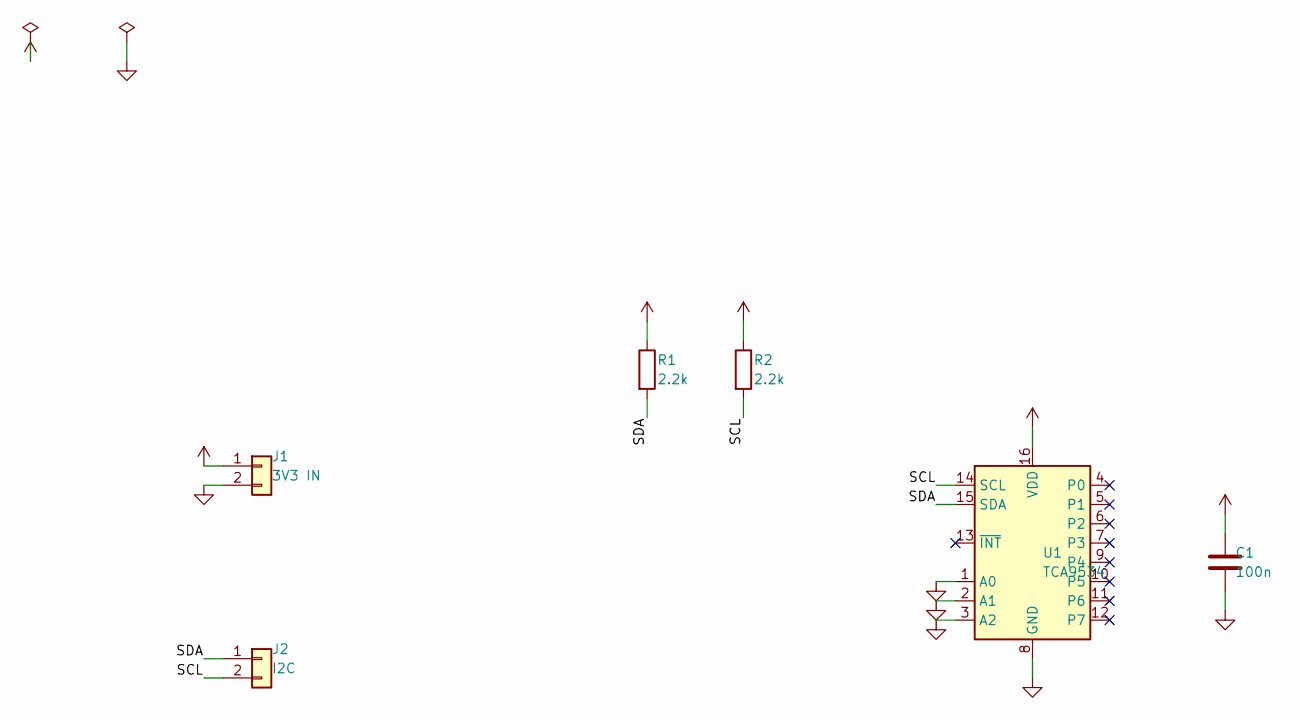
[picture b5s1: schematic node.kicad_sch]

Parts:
C1: 100n; C_0603_1608Metric
J1: 3V3 IN; PinHeader_1x02_P2.54mm_Vertical
J2: I2C; PinHeader_1x02_P2.54mm_Vertical
R1, R2: 2.2k; R_0603_1608Metric
U1: TCA9534; SOIC-16W_7.5x10.3mm_P1.27mm

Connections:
+3V3: C1.1, J1.1, R1.1, R2.1, U1.16 (VDD)
/SCL: J2.2, R2.2, U1.14 (SCL)
/SDA: J2.1, R1.2, U1.15 (SDA)
GND: C1.2, J1.2, U1.1 (A0), U1.2 (A1), U1.3 (A2), U1.8 (GND)

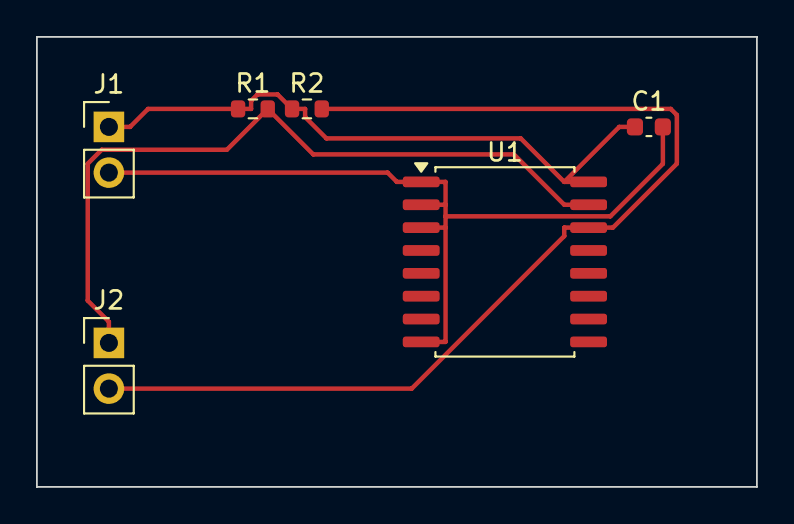
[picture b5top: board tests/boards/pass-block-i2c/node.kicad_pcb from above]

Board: 2 copper layers, 40.0 x 25.0 mm, 6 parts (0 on the bottom side), 4 nets.

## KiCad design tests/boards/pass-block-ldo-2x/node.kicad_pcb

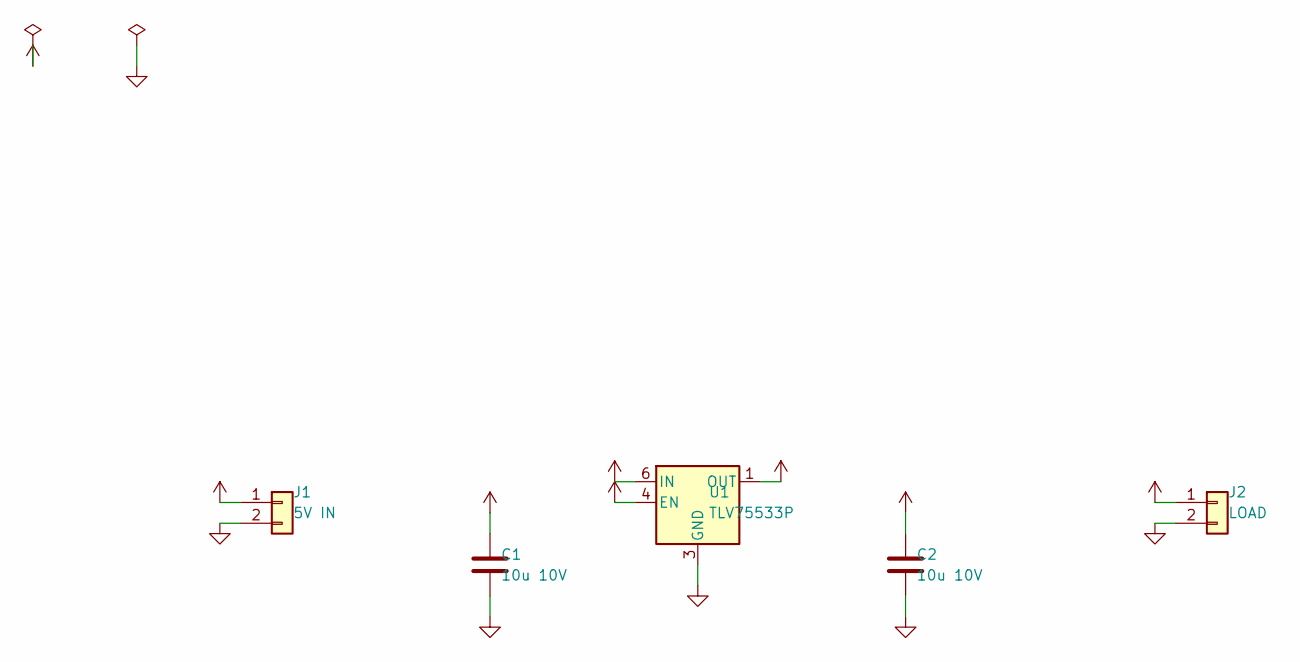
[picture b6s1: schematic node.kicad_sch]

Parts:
C1, C2: 10u 10V; C_0603_1608Metric
J1: 5V IN; PinHeader_1x02_P2.54mm_Vertical
J2: LOAD; PinHeader_1x02_P2.54mm_Vertical
U1: TLV75533P; WSON-6-1EP_2x2mm_P0.65mm_EP1x1.6mm

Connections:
+3V3: C2.1, J2.1, U1.1 (OUT)
+5V: C1.1, J1.1, U1.4 (EN), U1.6 (IN)
GND: C1.2, C2.2, J1.2, J2.2, U1.3 (GND), U1.7 (GND)

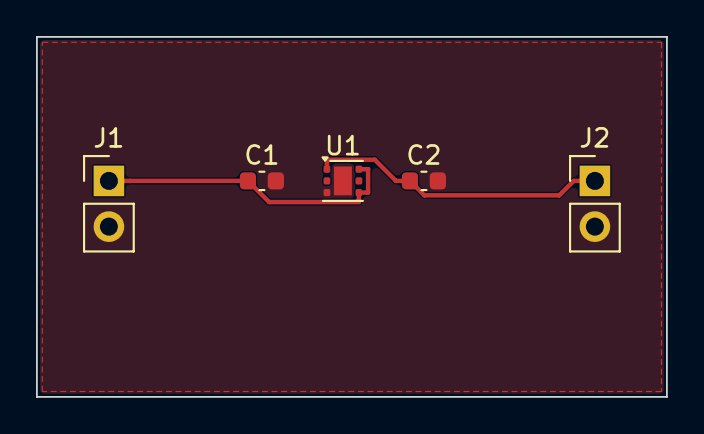
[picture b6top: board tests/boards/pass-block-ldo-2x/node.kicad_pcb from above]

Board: 2 copper layers, 35.0 x 20.0 mm, 5 parts (0 on the bottom side), 3 nets.

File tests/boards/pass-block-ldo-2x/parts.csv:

Value,Footprint,Qty,Manufacturer,MPN,Supplier,SKU,Pack,Breaks
TLV75533P,Package_SON:WSON-6-1EP_2x2mm_P0.65mm_EP1x1.6mm,1,Texas Instruments,TLV75533PDRVR,,,,
10u 10V,Capacitor_SMD:C_0603_1608Metric,2,Samsung,CL10A106KP8NNN,,,,

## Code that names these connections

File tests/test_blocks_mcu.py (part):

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def test_the_crystal_is_wired_to_the_terminals_its_maker_names():
    """ABS25 page 2: the crystal is between pins 1 and 4. Y1 is KiCad's Crystal_GND23 with XIN on pin 1
    and XOUT on pin 4. The symbol puts pins 2 and 3 at 1 point, so the schematic joins them: the block
    names that net Y1_G, and joins nothing else to it (Abracon: pins 2 and 3 float)."""
    d, _ = mcu()
    y1 = next(p for p in d.parts if p.ref == "Y1")
    assert (y1.symbol.lib_id, y1.nets) == (
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    d = built()
    next(p for p in d.parts if p.ref == "Y1").nets = {"1": "U1_XIN", "2": "U1_XOUT"}
    assert check(d) == [
        f"Y1: its terminals, pads 1 and 4, carry U1_XIN and none, not U1_XIN and U1_XOUT [{ABS25_PINS}]"
    ]
    assert check(built(Y1=None)) == [f"Y1: no crystal on the board [{EQ3}]"]

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

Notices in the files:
README.md:
License:
MIT; see [LICENSE](LICENSE). KiCad, ngspice, and FreeRouting keep their
own licenses. Inter, the website's font, is under the SIL Open Font
License: [site/fonts/LICENSE](site/fonts/LICENSE).
License: MIT
